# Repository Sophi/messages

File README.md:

# messages
WIP! Visit the project page
sophikravitz.com/messages

Messages from Space is an immersive sound installation built around a simple, true fact: cosmic rays from outer space are passing through your body right now. You cannot feel them. You cannot see them. But they are there. Our custom sensors measure these particles as they pass through the installation, activating sounds, lights, and stories all around you. Participants listen to the experience and view the lights and sculptures. They do not actively interact, but may pause along the path to rest, reflect, or watch the world unfold.

The installation is designed for one visitor or a small group moving at their own pace. Visitors move through several planetary sculptures (12” - 24” diameter) mounted at varying heights. The sculptures are arranged on a path held together by a gentle multi-channel ambient soundscape that gives the space a warm, immersive feeling. When a particle arrives from deep space and passes through a sculpture, roughly every few seconds, it activates a piece of the story, a conversation, a sound effect. Because the detections are real and random, no two experiences are identical: you might wait in silence between sculptures, or hear several conversations in quick succession.

The conversations belong to people living in the near-far future. They speak casually and intimately, sharing small moments of life in a world that is different but not unrecognizable, better in some ways, resilient and human. A doctor coaxing a child through heart surgery. Two centenarians rocking on a porch, remembering war. A young woman savoring chocolate that adapts to her tongue. An old man choosing which hip to replace.

Threading through all of it is Liz. Liz is 126 years old and has chosen the date of her death. Before she goes, she uploads her memories to the archive. She is your guide. Her voice connects the sculptures, reflecting on what she's witnessed across a century and a quarter of living, loving, losing, and staying connected through the Fire-Flood Years and the great dispersal, civilization-scale events that have reshaped the past hundred years.

Team:
Sofy Yuditskaya
Ria Rajan
Sophi Kravitz
Oliver Tanner

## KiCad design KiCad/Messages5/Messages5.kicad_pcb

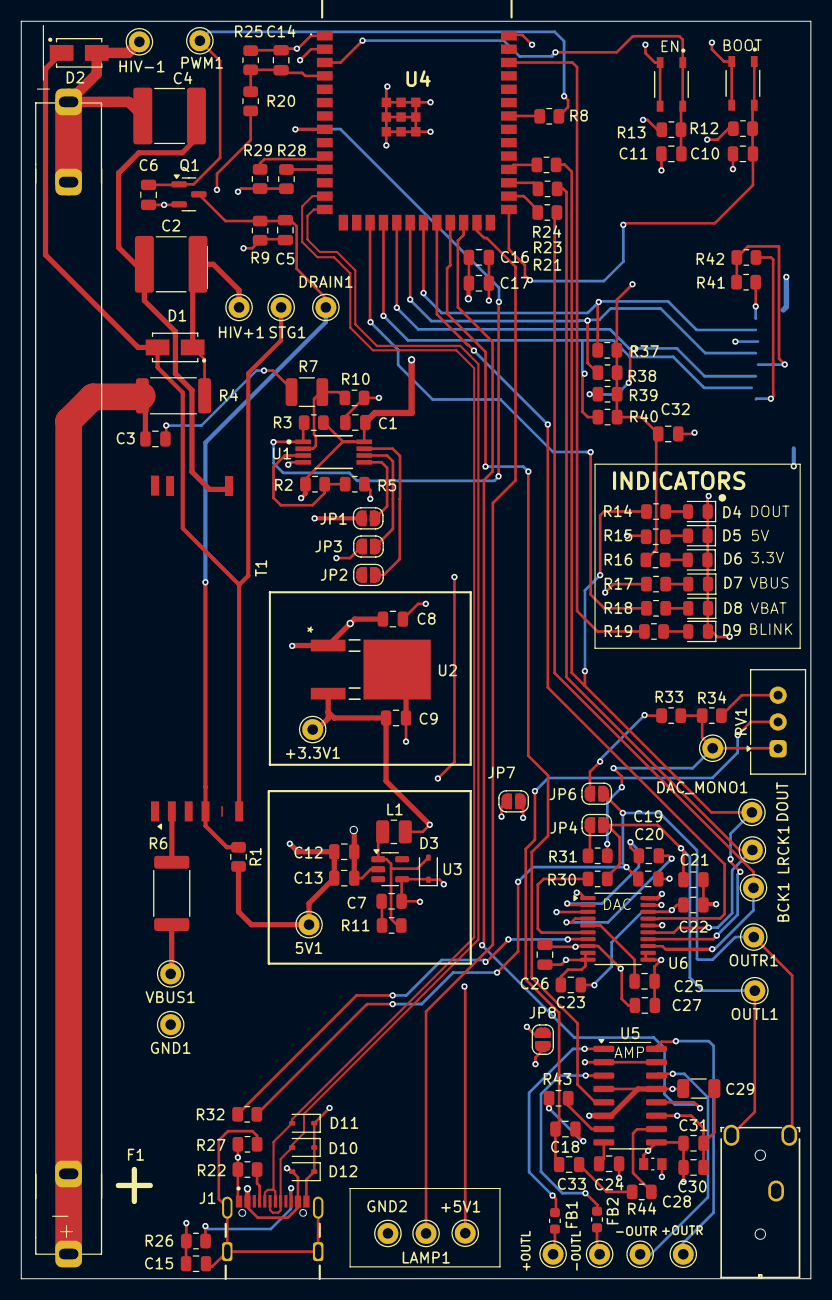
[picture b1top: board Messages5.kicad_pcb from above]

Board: 4 copper layers, 75.0 x 119.5 mm, 134 parts (1 on the bottom side), 81 nets.

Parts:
5V1: TestPoint; Pin_D1.0mm_L10.0mm
+3.3V1, +5V1: TestPoint; Pin_D1.0mm_L10.0mm
+OUTL: TestPoint; Pin_D1.0mm_L10.0mm
+OUTR: TestPoint; Pin_D1.0mm_L10.0mm
-OUTL: TestPoint; Pin_D1.0mm_L10.0mm
-OUTR: TestPoint; Pin_D1.0mm_L10.0mm
BCK1: TestPoint; Pin_D1.0mm_L10.0mm
C1, C10, C11, C14, C23, C27, C30: 0.1uF; C_0805_2012Metric
C2, C4: 1uF/ 500V; C_2220_5750Metric
C3, C5: 1000pF; C_0805_2012Metric
C6: 100pF; C_0805_2012Metric
C7: 120pF; C_0805_2012Metric
C8, C9, C12, C13, C16, C22, C26: 10uF; C_0805_2012Metric
C15: 0.01uF; C_0805_2012Metric
C17, C18, C24, C31, C32, C33: 1uF; C_0805_2012Metric
C19, C25: 2.2uF; C_0805_2012Metric
C20, C21: 2.2nF; C_0805_2012Metric
C28: 20uF; CAPC1810X80N
C29: 220uF; C_1206_3216Metric
D1, D2: ES1H; DIOM4226X244N
D3: D_Schottky; D_SOD-323
D4, D5, D6, D8, D9: YELLOW; LED_0805_2012Metric
D7: BLUE; LED_0805_2012Metric
D10, D11, D12: PESD5V0S1BA; D_SOD-323
DAC_MONO1: TestPoint; Pin_D1.0mm_L10.0mm
DOUT1: TestPoint; Pin_D1.0mm_L10.0mm
DRAIN1: TestPoint; Pin_D1.0mm_L10.0mm
F1: Clip; Fuseholder_Clip-7.62mm_Littelfuse
FB1, FB2: FerriteBead_Small; L_0603_1608Metric
GND1, GND2: TestPoint; Pin_D1.0mm_L10.0mm
HIV+1: TestPoint; Pin_D1.0mm_L10.0mm
HIV-1: TestPoint; Pin_D1.0mm_L10.0mm
J1: USB4105-GF-A; GCT_USB4105-GF-A
J2: AUDIO JACK; STX-3000_KYC
J3: MEM2061-01-188-00-A; MEM2061-01-188-00-A_GCT
JP1, JP2, JP3, JP4, JP6, JP7, JP8: SolderJumper_2_Open; SolderJumper-2_P1.3mm_Open_RoundedPad1.0x1.5mm
L1: 2.2uH; L_1008_2520Metric
LAMP1: TestPoint; Pin_D1.0mm_L10.0mm
LRCK1: TestPoint; Pin_D1.0mm_L10.0mm
OUTL1: TestPoint; Pin_D1.0mm_L10.0mm
OUTR1: TestPoint; Pin_D1.0mm_L10.0mm
PWM1: TestPoint; Pin_D1.0mm_L10.0mm
Q1: AO3400A; SOT-23
R1, R14, R15, R16, R17, R18, R19: 220R; R_0805_2012Metric
R2: 22k; R_0805_2012Metric
R3, R5, R10, R12, R13, R25, R28, R29, R31, R33, R34, R43, R44: 10k; R_0805_2012Metric
R4: 560k, 1M; R_2512_6332Metric
R6: 10R; R_2512_6332Metric
R7: 1M; R_1210_3225Metric
R8: 1K; R_0805_2012Metric
R9: 100R; R_0805_2012Metric
R11: 10R; R_0805_2012Metric
R20: 2.7k; R_0805_2012Metric
R21, R23, R24: 33R; R_0805_2012Metric
R22, R26: 5.1k; R_0805_2012Metric
R27: 1M; R_0805_2012Metric
R30, R32: 470R; R_0805_2012Metric
R37, R38, R39, R40, R41, R42: 4.7k; R_0805_2012Metric
RV1: R_Potentiometer; Potentiometer_Vishay_T93YA_Vertical
S1, S2: SKRPABE010; SW_SKRPABE010
STG1: TestPoint; Pin_D1.0mm_L10.0mm
T1: FL2810-1L; Transformer_Coilcraft_FL2810-1L
U1: LM393BIPWR; PW0008A-MFG
U2: AP7363-33D-13; TO252-3L_DIO
U3: TPS613222ADBV; SOT-23-5
U4: ESP32-S3-WROOM-1-N8; ESP32S3WROOM1N8R2
U5: PAM8406DR; SOP-16_3.9x9.9mm_P1.27mm
U6: PCM5102; TSSOP-20_4.4x6.5mm_P0.65mm
VBUS1: TestPoint; Pin_D1.0mm_L10.0mm

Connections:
+3.3V: +3.3V1.1, C1.2, C9.1, C16.1, C17.1, C26.1, C27.1, C32.1, J3.P4 (VDD), JP1.2 (B), L1.1, R2.2, R3.2, R12.2, R13.2, R16.2, R28.2, R29.2, R37.1, R38.1, R39.1, R40.1, R41.2, R42.2, U1.8 (VCC), U2.3 (OUT), U4.2 (3V3), U6.1 (CPVDD), U6.8 (AVDD), U6.20 (DVDD)
+5V: 5V1.1, +5V1.1, C7.1, C12.1, C13.1, D3.1 (K), R1.2, R15.2, U3.4 (VOUT)
/AMP: U4.24 (IO47), U5.12 (~SHND)
/Audio4/AMP_MONO: C18.2, C33.2, RV1.2
/Audio4/DAC_MONO: DAC_MONO1.1, R31.1, R33.1, R34.1, RV1.1
/Audio4/OUTL: C21.1, J2.2, JP4.2 (B), OUTL1.1, R30.1
/Audio4/OUTR: C20.1, J2.3, JP6.2 (B), OUTR1.1, R32.1
/Audio4/POT_OUTL: R43.1, U5.7 (INL)
/Audio4/POT_OUTR: R44.1, U5.10 (INR)
/BAT_SENSE: R18.2, U4.17 (IO9)
/BLINK: R19.2, U4.38 (IO2)
/CS: J3.P2 (DAT3/CS), R40.2, U4.18 (IO10/CS)
/EN: C11.2, R13.1, S2.1, S2.2, U4.3 (EN)
/GPIO0: C10.2, R12.1, S1.1, S1.2, U4.27 (IO0)
/I2S_BCK: BCK1.1, R21.1, U6.13 (BCK)
/I2S_DOUT: DOUT1.1, R14.2, R24.1, U6.14 (DIN)
/I2S_LRCK: LRCK1.1, R23.1, U6.15 (LRCK)
/LAMP: LAMP1.1, U4.25 (IO48)
/MCU4/SHELL_GND: C15.2, J1.SH1 (SHELL_GND), J1.SH2 (SHELL_GND), J1.SH3 (SHELL_GND), J1.SH4 (SHELL_GND), R27.1
/MISO: J3.P7 (DAT0/MISO), R37.2, U4.21 (IO13/MISO)
/MOSI: J3.P3 (CMD/MOSI), R39.2, U4.19 (IO11/MOSI)
/MUTE: U4.22 (IO14), U6.17 (XSMT)
/MUTE_AMP: U4.23 (IO21), U5.5 (~MUTE)
/PWM: R8.2, U4.34 (IO41)
/Power4/ANODE: C3.1, F1.1, R4.1
/Power4/CATHODE: C4.1, D2.2 (A), F1.2, HIV-1.1
/RAD_IN: R3.1, U1.1 (1OUT), U4.8 (IO15)
/SCK: J3.P5 (SCLK), R38.2, U4.20 (IO12/CLK)
/SCL: R29.1, U4.10 (IO17)
/SDA: R28.1, U4.11 (IO18)
/USB_D+: D10.2, J1.A6 (DP+), J1.B6 (DP2+), U4.14 (IO20)
/USB_D-: D11.2, J1.A7 (DN-), J1.B7 (DN2-), U4.13 (IO19)
AGND: C20.2, C21.2, C22.2, C23.2, C25.2, C26.2, C27.2, J2.1, JP7.1 (A), JP8.2 (B), R34.2, RV1.3, U6.3 (CPGND), U6.9 (AGND), U6.10 (DEMP), U6.11 (FLT), U6.12 (SCK), U6.16 (FMT), U6.19 (DGND)
GND: C1.1, C5.2, C6.2, C8.2, C9.2, C10.1, C11.1, C12.2, C13.2, C14.2, C15.1, C16.2, C17.2, C32.2, D4.1 (K), D5.1 (K), D6.1 (K), D7.1 (K), D8.1 (K), D9.1 (K), D10.1, D11.1, D12.1, GND1.1, GND2.1, J1.A1_B12 (GND), J1.B1_A12 (GND), J3.11 (GROUND), J3.12 (GROUND), J3.P6 (VSS), JP3.2 (B), JP7.2 (B), Q1.2 (S), R5.1, R9.1, R10.1, R22.2, R25.1, R26.2, R27.2, S1.3, S1.4, S2.3, S2.4, U1.4 (GND), U2.2 (GND), U3.2 (GND), U4.1 (GND_1), U4.40 (GND_2), U4.41 (GND_3), U4.42 (GND_4), U4.43 (GND_5), U4.44 (GND_6), U4.45 (GND_7), U4.46 (GND_8), U4.47 (GND_9), U4.48 (GND_10), U4.49 (GND_11)
unnamed: +OUTL.1, FB1.1
unnamed: -OUTL.1, FB2.1
unnamed: C2.1, C4.2, T1.7
unnamed: C3.2, R7.2
unnamed: C7.2, R11.1
unnamed: C18.1, R43.2
unnamed: C33.1, R44.2
unnamed: D1.2 (A), D2.1 (K), STG1.1, T1.6
unnamed: C2.2, D1.1 (K), HIV+1.1, R4.2
unnamed: D3.2 (A), L1.2, R11.2, U3.1 (SW)
unnamed: D4.2 (A), R14.1
unnamed: D5.2 (A), R15.1
unnamed: D6.2 (A), R16.1
unnamed: D7.2 (A), R17.1
unnamed: D8.2 (A), R18.1
unnamed: D9.2 (A), R19.1
unnamed: J1.A5 (CC1), R22.1
unnamed: J1.B5 (CC2), R26.1
unnamed: J3.P8 (DAT1), R41.1
unnamed: J3.P1 (DAT2), R42.1
unnamed: JP1.1 (A), U1.5 (2IN+)
unnamed: JP2.2 (B), U1.7 (2OUT)
unnamed: JP3.1 (A), U1.6 (2IN-)
unnamed: JP4.1 (A), R31.2
unnamed: JP6.1 (A), R33.2
unnamed: C5.1, DRAIN1.1, Q1.3 (D), R1.1, R9.2, T1.4
unnamed: C6.1, PWM1.1, Q1.1 (G), R8.1
unnamed: R6.1, T1.2
unnamed: R2.1, R5.2, U1.3 (1IN+)
unnamed: R7.1, R10.2, U1.2 (1IN-)
unnamed: C14.1, R20.1, R25.2, U4.4 (IO4/ADC1_CH3)
unnamed: R21.2, U4.28 (IO35)
unnamed: R23.2, U4.29 (IO36)
unnamed: R24.2, U4.30 (IO37)
unnamed: FB1.2, U5.1 (+OUT_L)
unnamed: +OUTR.1, U5.16 (+OUT_R)
unnamed: FB2.2, U5.3 (-OUT_L)
unnamed: -OUTR.1, U5.14 (-OUT_R)
unnamed: C24.1, U5.8 (VREF)
unnamed: C19.2, U6.4 (CAPM)
unnamed: C19.1, U6.2 (CAPP)
unnamed: C22.1, C23.1, U6.18 (LDOO)
unnamed: R30.2, U6.6 (OUTL)
unnamed: R32.2, U6.7 (OUTR)
unnamed: C25.1, U6.5 (VNEG)
PGND: C24.2, C28.2, C29.2, C30.2, C31.2, JP8.1 (A), U5.2 (PGNDL), U5.11 (GND), U5.15 (PGNDR)
VBUS: C8.1, C28.1, C29.1, C30.1, C31.1, D12.2, J1.A4_B9 (VBUS), J1.B4_A9 (VBUS), R6.2, R17.2, R20.2, U2.1 (IN), U5.4 (PVDDL), U5.6 (VDD), U5.9 (MODE), U5.13 (PVDDR), VBUS1.1

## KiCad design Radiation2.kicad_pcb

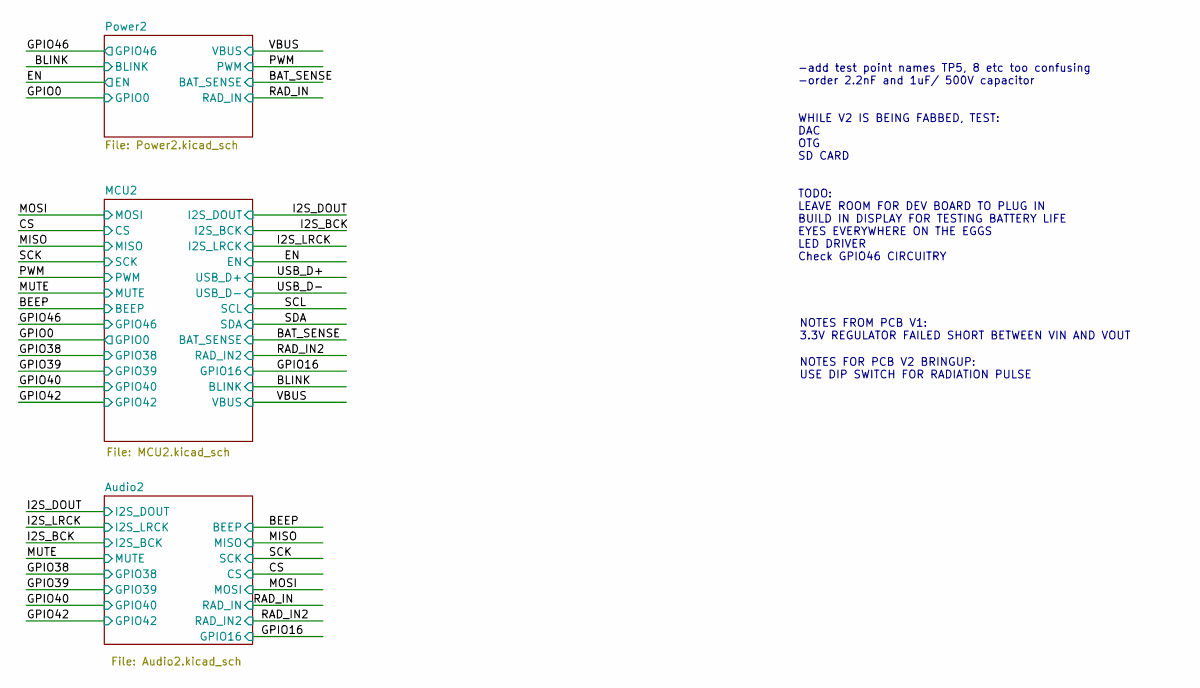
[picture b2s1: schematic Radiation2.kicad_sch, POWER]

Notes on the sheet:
-add test point names TP5, 8 etc too confusing -order 2.2nF and 1uF/ 500V capacitor WHILE V2 IS BEING FABBED, TEST: DAC OTG SD CARD TODO: LEAVE ROOM FOR DEV BOARD TO PLUG IN BUILD IN DISPLAY FOR TESTING BATTERY LIFE EYES EVERYWHERE ON THE EGGS LED DRIVER Check GPIO46 CIRCUITRY
NOTES FOR PCB V2 BRINGUP: USE DIP SWITCH FOR RADIATION PULSE
NOTES FROM PCB V1: 3.3V REGULATOR FAILED SHORT BETWEEN VIN AND VOUT

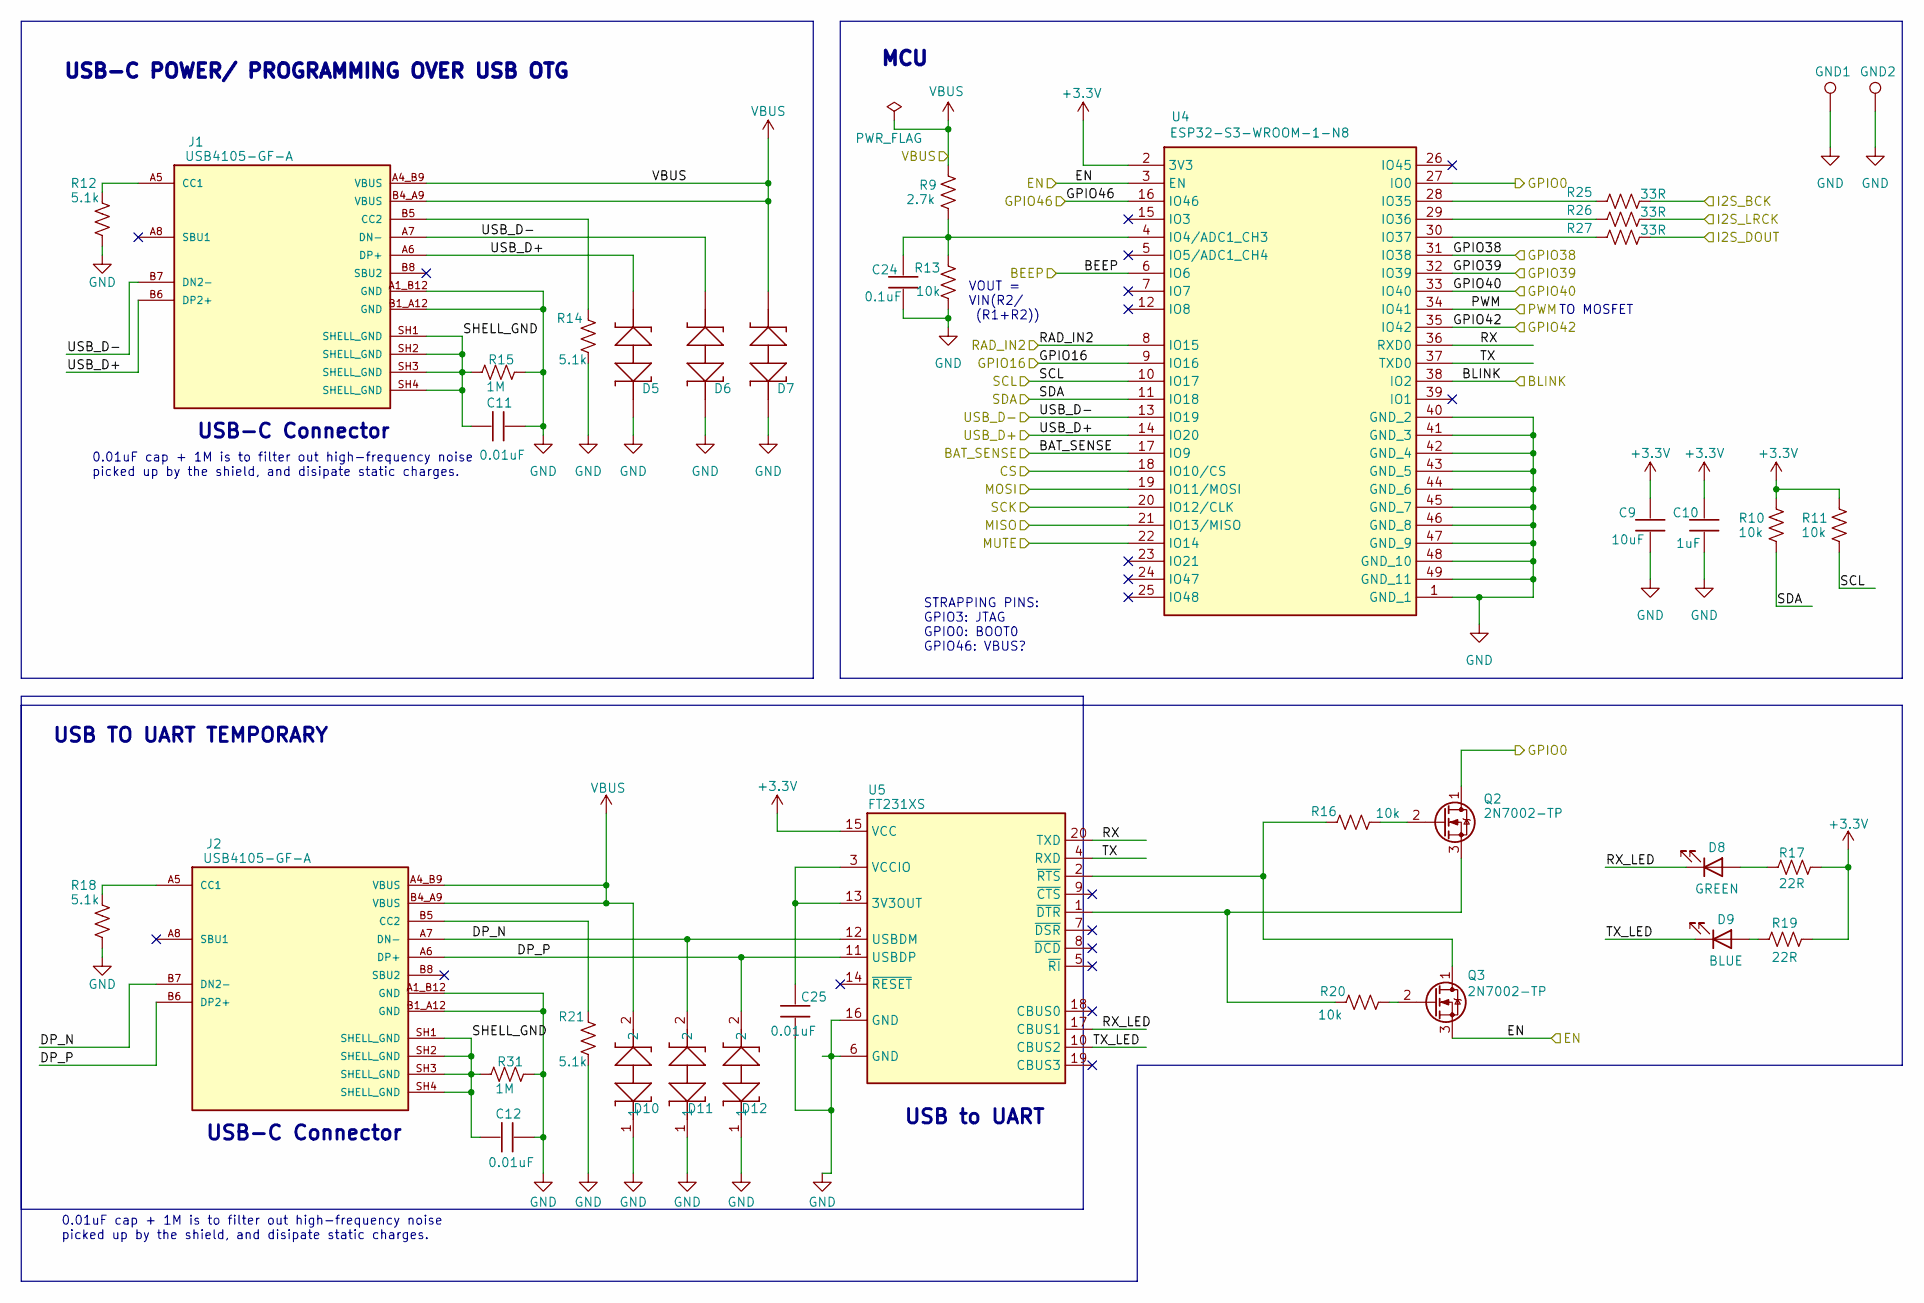
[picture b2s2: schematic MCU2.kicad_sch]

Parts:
C9: 10uF; C_0805_2012Metric; MPN CL21B106KPQNNNE
C10: 1uF; C_0805_2012Metric; MPN CC0805KKX5R6BB105
C11, C12, C25: 0.01uF; C_0805_2012Metric; MPN C0805C103K5RACTU
C24: 0.1uF; C_0805_2012Metric; MPN CC0805KRX7R9BB104
D5, D6, D7, D10, D11, D12: PESD5V0S1BA; SOD323_NXP; MPN PESD5V0S1BA,115
D8: GREEN; LED_0805_2012Metric; MPN 150080GS75000
D9: BLUE; LED_0805_2012Metric; MPN 150080BS75000
GND1, GND2: TestPoint; Pin_D1.0mm_L10.0mm
J1, J2: USB4105-GF-A; GCT_USB4105-GF-A; MPN USB4105-GF-A
Q2, Q3: 2N7002-TP; SOT-23; MPN 2N7002-TP
R9: 2.7k; R_0805_2012Metric; MPN CRG0805F2K7
R10, R11, R13, R16, R20: 10k; R_0805_2012Metric; MPN RMCF0805FT10K0
R12, R14, R18, R21: 5.1k; R_0805_2012Metric; MPN RC0805JR-075K1L
R15, R31: 1M; R_0805_2012Metric; MPN RC0805JR-071ML
R17, R19: 22R; R_0805_2012Metric; MPN RC0805FR-0722RL
R25, R26, R27: 33R; R_0805_2012Metric; MPN RC0805FR-0733RL
U4: ESP32-S3-WROOM-1-N8; ESP32S3WROOM1N8R2; Mouser Part Number 356-ESP32-S3WROOM1N8
U5: FT231XS; SSOP-20_3.9x8.7mm_P0.635mm; MPN FT231XS-R

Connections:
+3.3V: C9.1, C10.1, R10.2, R11.2, R17.1, R19.1, U4.2 (3V3), U5.15 (VCC); also elsewhere on the board
/BAT_SENSE: U4.17 (IO9); also elsewhere on the board
/BEEP: U4.6 (IO6); also elsewhere on the board
/BLINK: U4.38 (IO2); also elsewhere on the board
/CS: U4.18 (IO10/CS); also elsewhere on the board
/EN: Q3.3 (S), U4.3 (EN); also elsewhere on the board
/GPIO0: Q2.1 (D), U4.27 (IO0); also elsewhere on the board
/GPIO16: U4.9 (IO16); also elsewhere on the board
/GPIO38: U4.31 (IO38); also elsewhere on the board
/GPIO39: U4.32 (IO39); also elsewhere on the board
/GPIO40: U4.33 (IO40); also elsewhere on the board
/GPIO42: U4.35 (IO42); also elsewhere on the board
/GPIO46: U4.16 (IO46); also elsewhere on the board
/I2S_BCK: R25.1; also elsewhere on the board
/I2S_DOUT: R27.1; also elsewhere on the board
/I2S_LRCK: R26.1; also elsewhere on the board
/MCU2/DP_N: D11.2, J2.A7 (DN-), J2.B7 (DN2-), U5.12 (USBDM)
/MCU2/DP_P: D12.2, J2.A6 (DP+), J2.B6 (DP2+), U5.11 (USBDP)
/MCU2/RX: U4.36 (RXD0), U5.20 (TXD)
/MCU2/RX_LED: D8.1 (K), U5.17 (CBUS1)
/MCU2/SHELL_GND: C11.2, C12.2, J1.SH1 (SHELL_GND), J1.SH2 (SHELL_GND), J1.SH3 (SHELL_GND), J1.SH4 (SHELL_GND), J2.SH1 (SHELL_GND), J2.SH2 (SHELL_GND), J2.SH3 (SHELL_GND), J2.SH4 (SHELL_GND), R15.1, R31.1
/MCU2/TX: U4.37 (TXD0), U5.4 (RXD)
/MCU2/TX_LED: D9.1 (K), U5.10 (CBUS2)
/MISO: U4.21 (IO13/MISO); also elsewhere on the board
/MOSI: U4.19 (IO11/MOSI); also elsewhere on the board
/MUTE: U4.22 (IO14); also elsewhere on the board
/PWM: U4.34 (IO41); also elsewhere on the board
/RAD_IN2: U4.8 (IO15); also elsewhere on the board
/SCK: U4.20 (IO12/CLK); also elsewhere on the board
/SCL: R11.1, U4.10 (IO17)
/SDA: R10.1, U4.11 (IO18)
/USB_D+: D5.2, J1.A6 (DP+), J1.B6 (DP2+), U4.14 (IO20)
/USB_D-: D6.2, J1.A7 (DN-), J1.B7 (DN2-), U4.13 (IO19)
GND: C9.2, C10.2, C11.1, C12.1, C24.2, C25.1, D5.1, D6.1, D7.1, D10.1, D11.1, D12.1, GND1.1, GND2.1, J1.A1_B12 (GND), J1.B1_A12 (GND), J2.A1_B12 (GND), J2.B1_A12 (GND), R12.2, R13.1, R14.2, R15.2, R18.2, R21.2, R31.2, U4.1 (GND_1), U4.40 (GND_2), U4.41 (GND_3), U4.42 (GND_4), U4.43 (GND_5), U4.44 (GND_6), U4.45 (GND_7), U4.46 (GND_8), U4.47 (GND_9), U4.48 (GND_10), U4.49 (GND_11), U5.6 (GND), U5.16 (GND); also elsewhere on the board
unnamed: D8.2 (A), R17.2
unnamed: D9.2 (A), R19.2
unnamed: J1.A5 (CC1), R12.1
unnamed: J1.B5 (CC2), R14.1
unnamed: J2.A5 (CC1), R18.1
unnamed: J2.B5 (CC2), R21.1
unnamed: Q2.2 (G), R16.1
unnamed: Q2.3 (S), R20.2, U5.1 (~DTR)
unnamed: Q3.1 (D), R16.2, U5.2 (~RTS)
unnamed: Q3.2 (G), R20.1
unnamed: C24.1, R9.1, R13.2, U4.4 (IO4/ADC1_CH3)
unnamed: R25.2, U4.28 (IO35)
unnamed: R26.2, U4.29 (IO36)
unnamed: R27.2, U4.30 (IO37)
unnamed: C25.2, U5.3 (VCCIO), U5.13 (3V3OUT)
VBUS: D7.2, D10.2, J1.A4_B9 (VBUS), J1.B4_A9 (VBUS), J2.A4_B9 (VBUS), J2.B4_A9 (VBUS), R9.2; also elsewhere on the board

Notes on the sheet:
USB-C POWER/ PROGRAMMING OVER USB OTG
0.01uF cap + 1M is to filter out high-frequency noise picked up by the shield, and disipate static charges.
MCU
VOUT = VIN(R2/ (R1+R2))
USB TO UART TEMPORARY
TO MOSFET
USB-C Connector
STRAPPING PINS: GPIO3: JTAG GPIO0: BOOT0 GPIO46: VBUS?
USB to UART

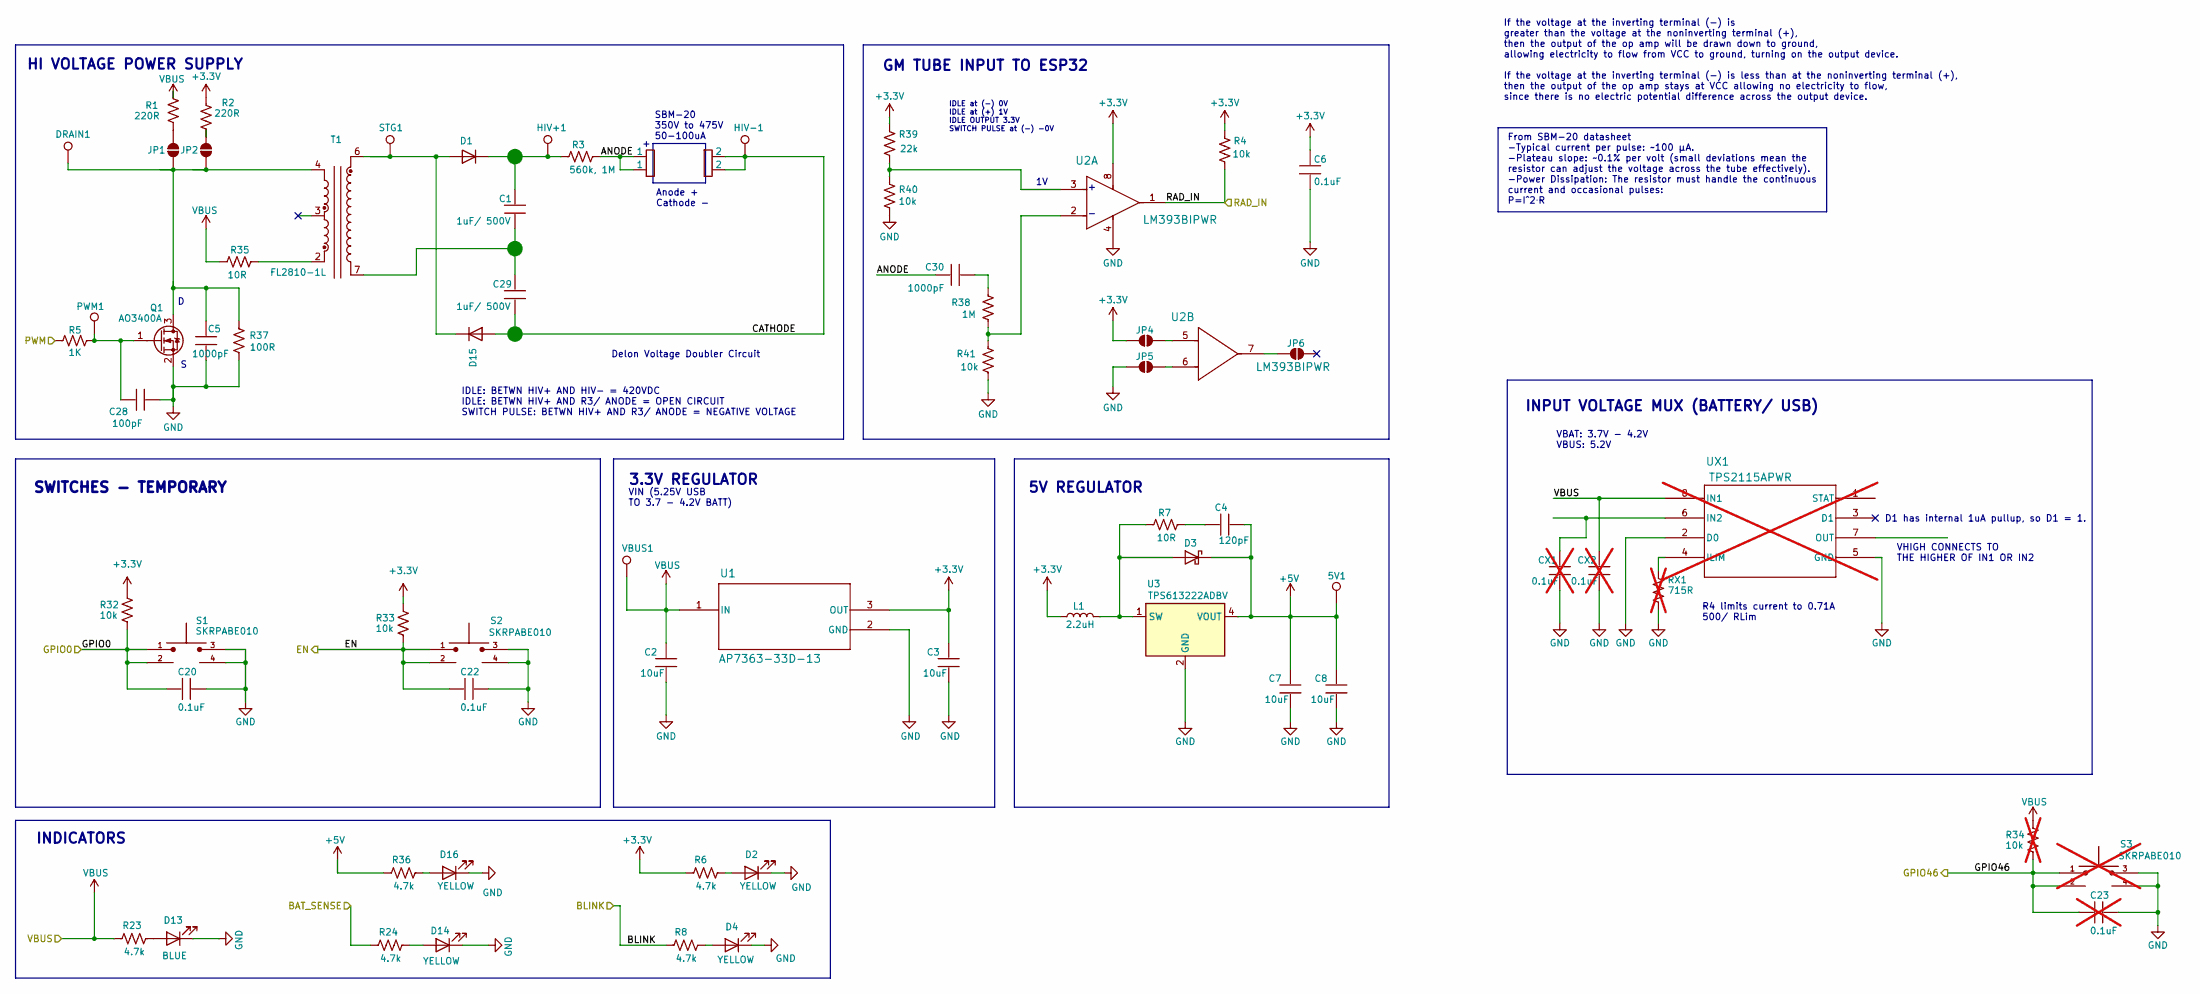
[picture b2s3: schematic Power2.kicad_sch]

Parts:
5V1: TestPoint; Pin_D1.0mm_L10.0mm
C1, C29: 1uF/ 500V; C_2220_5750Metric; MPN ECW-FD2J105K
C2, C3, C7, C8: 10uF; C_0805_2012Metric; MPN CL21B106KPQNNNE
C4: 120pF; C_0805_2012Metric; MPN C0805C121J5GACTU
C5, C30: 1000pF; C_0805_2012Metric; MPN C2012C0G2W102J060AA
C6, C20, C22: 0.1uF; C_0805_2012Metric; MPN CC0805KRX7R9BB104
C23: 0.1uF; C_0805_2012Metric; MPN CC0805KRX7R9BB104; not fitted
C28: 100pF; C_0805_2012Metric; MPN C0805C101J5GACTU
CX1, CX2: 0.1uF; C_0805_2012Metric; MPN CC0805KRX7R9BB104; not fitted
D1, D15: ES1H; DIOM4226X244N; MPN ES1H
D2, D4, D14, D16: YELLOW; LED_0805_2012Metric; MPN 150080YS75000
D3: D_Schottky; D_SOD-323; MPN 1SS367,H3F
D13: BLUE; LED_0805_2012Metric; MPN 150080BS75000
DRAIN1: TestPoint; Pin_D1.0mm_L10.0mm
F1: Clip; Fuseholder_Clip-7.62mm_Littelfuse; MPN 01220088Z
HIV+1: TestPoint; Pin_D1.0mm_L10.0mm
HIV-1: TestPoint; Pin_D1.0mm_L10.0mm
JP1, JP2, JP4, JP5, JP6: SolderJumper_2_Open; SolderJumper-2_P1.3mm_Open_RoundedPad1.0x1.5mm
L1: 2.2uH; L_1008_2520Metric; MPN DFE252012F-2R2M=P2
PWM1: TestPoint; Pin_D1.0mm_L10.0mm
Q1: AO3400A; SOT-23; MPN AO3400A
R1, R2: 220R; R_0805_2012Metric; MPN RK73B2ATTD221J
R3: 560k, 1M; R_2512_6332Metric; MPN CRGP2512F560K
R4: 10k; R_0805_2012Metric; MPN CRCW08054K70FKEAC
R5: 1K; R_0805_2012Metric; MPN RNCP0805FTD1K00
R6, R8, R23, R24, R36: 4.7k; R_0805_2012Metric; MPN CRCW08054K70FKEAC
R7: 10R; R_0805_2012Metric; MPN RMCF0603FT10R0
R32, R33, R40, R41: 10k; R_0805_2012Metric; MPN RMCF0805FT10K0
R34: 10k; R_0805_2012Metric; MPN RMCF0805FT10K0; not fitted
R35: 10R; R_2512_6332Metric; MPN 352210RJT
R37: 100R; R_0805_2012Metric; MPN ERJ-P06J101V
R38: 1M; R_1210_3225Metric; MPN RC1210FR-071ML
R39: 22k; R_0805_2012Metric; MPN RMCF0805JT22K0
RX1: 715R; R_0805_2012Metric; MPN CRCW0805715RFKEA; not fitted
S1, S2: SKRPABE010; SW_SKRPABE010; MPN SKRPABE010
S3: SKRPABE010; SW_SKRPABE010; MPN SKRPABE010; not fitted
STG1: TestPoint; Pin_D1.0mm_L10.0mm
T1: FL2810-1L; Transformer_Coilcraft_FL2810-1L; MPN FL2810-1L; Mouser Part Number 580-54100C
U1: AP7363-33D-13; TO252-3L_DIO
U2: LM393BIPWR; PW0008A-MFG
U3: TPS613222ADBV; SOT-23-5; MPN TPS613222ADBV
UX1: TPS2115APWR; PW8; MPN TPS2115APWR; not fitted
VBUS1: TestPoint; Pin_D1.0mm_L10.0mm

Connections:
+3.3V: C3.1, C6.2, JP4.2 (B), L1.1, R2.2, R4.2, R6.2, R32.2, R33.2, R39.2, U1.3 (OUT), U2.8 (VCC); also elsewhere on the board
+5V: 5V1.1, C4.1, C7.1, C8.1, D3.1 (K), R36.2, U3.4 (VOUT)
/BAT_SENSE: R24.2; also elsewhere on the board
/BLINK: R8.2; also elsewhere on the board
/EN: C22.2, R33.1, S2.1, S2.2; also elsewhere on the board
/GPIO0: C20.2, R32.1, S1.1, S1.2; also elsewhere on the board
/GPIO46: C23.2, R34.1, S3.1, S3.2; also elsewhere on the board
/PWM: R5.2; also elsewhere on the board
/Power2/ANODE: C30.1, F1.1, R3.1
/Power2/CATHODE: C29.1, D15.2 (A), F1.2, HIV-1.1
/RAD_IN: R4.1, U2.1 (1OUT); also elsewhere on the board
GND: C2.2, C3.2, C5.2, C6.1, C7.2, C8.2, C20.1, C22.1, C23.1, C28.2, CX1.2, CX2.2, D2.1 (K), D4.1 (K), D13.1 (K), D14.1 (K), D16.1 (K), JP5.2 (B), Q1.2 (S), R37.1, R40.1, R41.1, RX1.1, S1.3, S1.4, S2.3, S2.4, S3.3, S3.4, U1.2 (GND), U2.4 (GND), U3.2 (GND), UX1.2 (D0), UX1.5 (GND); also elsewhere on the board
unnamed: C1.1, C29.2, T1.7
unnamed: C4.2, R7.1
unnamed: C30.2, R38.2
unnamed: CX1.1, UX1.6 (IN2)
unnamed: CX2.1, UX1.8 (IN1)
unnamed: D1.2 (A), D15.1 (K), STG1.1, T1.6
unnamed: C1.2, D1.1 (K), HIV+1.1, R3.2
unnamed: D2.2 (A), R6.1
unnamed: D3.2 (A), L1.2, R7.2, U3.1 (SW)
unnamed: D4.2 (A), R8.1
unnamed: D13.2 (A), R23.1
unnamed: D14.2 (A), R24.1
unnamed: D16.2 (A), R36.1
unnamed: C5.1, DRAIN1.1, JP1.1 (A), JP2.1 (A), Q1.3 (D), R37.2, T1.4
unnamed: JP1.2 (B), R1.1
unnamed: JP2.2 (B), R2.1
unnamed: JP4.1 (A), U2.5 (2IN+)
unnamed: JP5.1 (A), U2.6 (2IN-)
unnamed: JP6.2 (B), U2.7 (2OUT)
unnamed: C28.1, PWM1.1, Q1.1 (G), R5.1
unnamed: R35.1, T1.2
unnamed: RX1.2, UX1.4 (ILIM)
unnamed: R39.1, R40.2, U2.3 (1IN+)
unnamed: R38.1, R41.2, U2.2 (1IN-)
VBUS: C2.1, R1.2, R23.2, R34.2, R35.2, U1.1 (IN), VBUS1.1; also elsewhere on the board

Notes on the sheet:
5V REGULATOR
D1 has internal 1uA pullup, so D1 = 1.
GM TUBE INPUT TO ESP32
INPUT VOLTAGE MUX (BATTERY/ USB)
INDICATORS
HI VOLTAGE POWER SUPPLY
If the voltage at the inverting terminal (-) is greater than the voltage at the noninverting terminal (+), then the output of the op amp will be drawn down to ground, allowing electricity to flow from VCC to ground, turning on the output device. If the voltage at the inverting terminal (-) is less 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
Delon Voltage Doubler Circuit
From SBM-20 datasheet -Typical current per pulse: ~100 µA. -Plateau slope: ~0.1% per volt (small deviations mean the resistor can adjust the voltage across the tube effectively). -Power Dissipation: The resistor must handle the continuous current and occasional pulses: P=I^2⋅R
R4 limits current to 0.71A 500/ RLim
VIN (5.25V USB TO 3.7 - 4.2V BATT)
3.3V REGULATOR
VHIGH CONNECTS TO THE HIGHER OF IN1 OR IN2
SWITCHES - TEMPORARY
Anode + Cathode -
VBAT: 3.7V - 4.2V VBUS: 5.2V
SBM-20 350V to 475V 50-100uA
IDLE at (-) 0V IDLE at (+) 1V IDLE OUTPUT 3.3V SWITCH PULSE at (-) -0V
IDLE: BETWN HIV+ AND HIV- = 420VDC IDLE: BETWN HIV+ AND R3/ ANODE = OPEN CIRCUIT SWITCH PULSE: BETWN HIV+ AND R3/ ANODE = NEGATIVE VOLTAGE

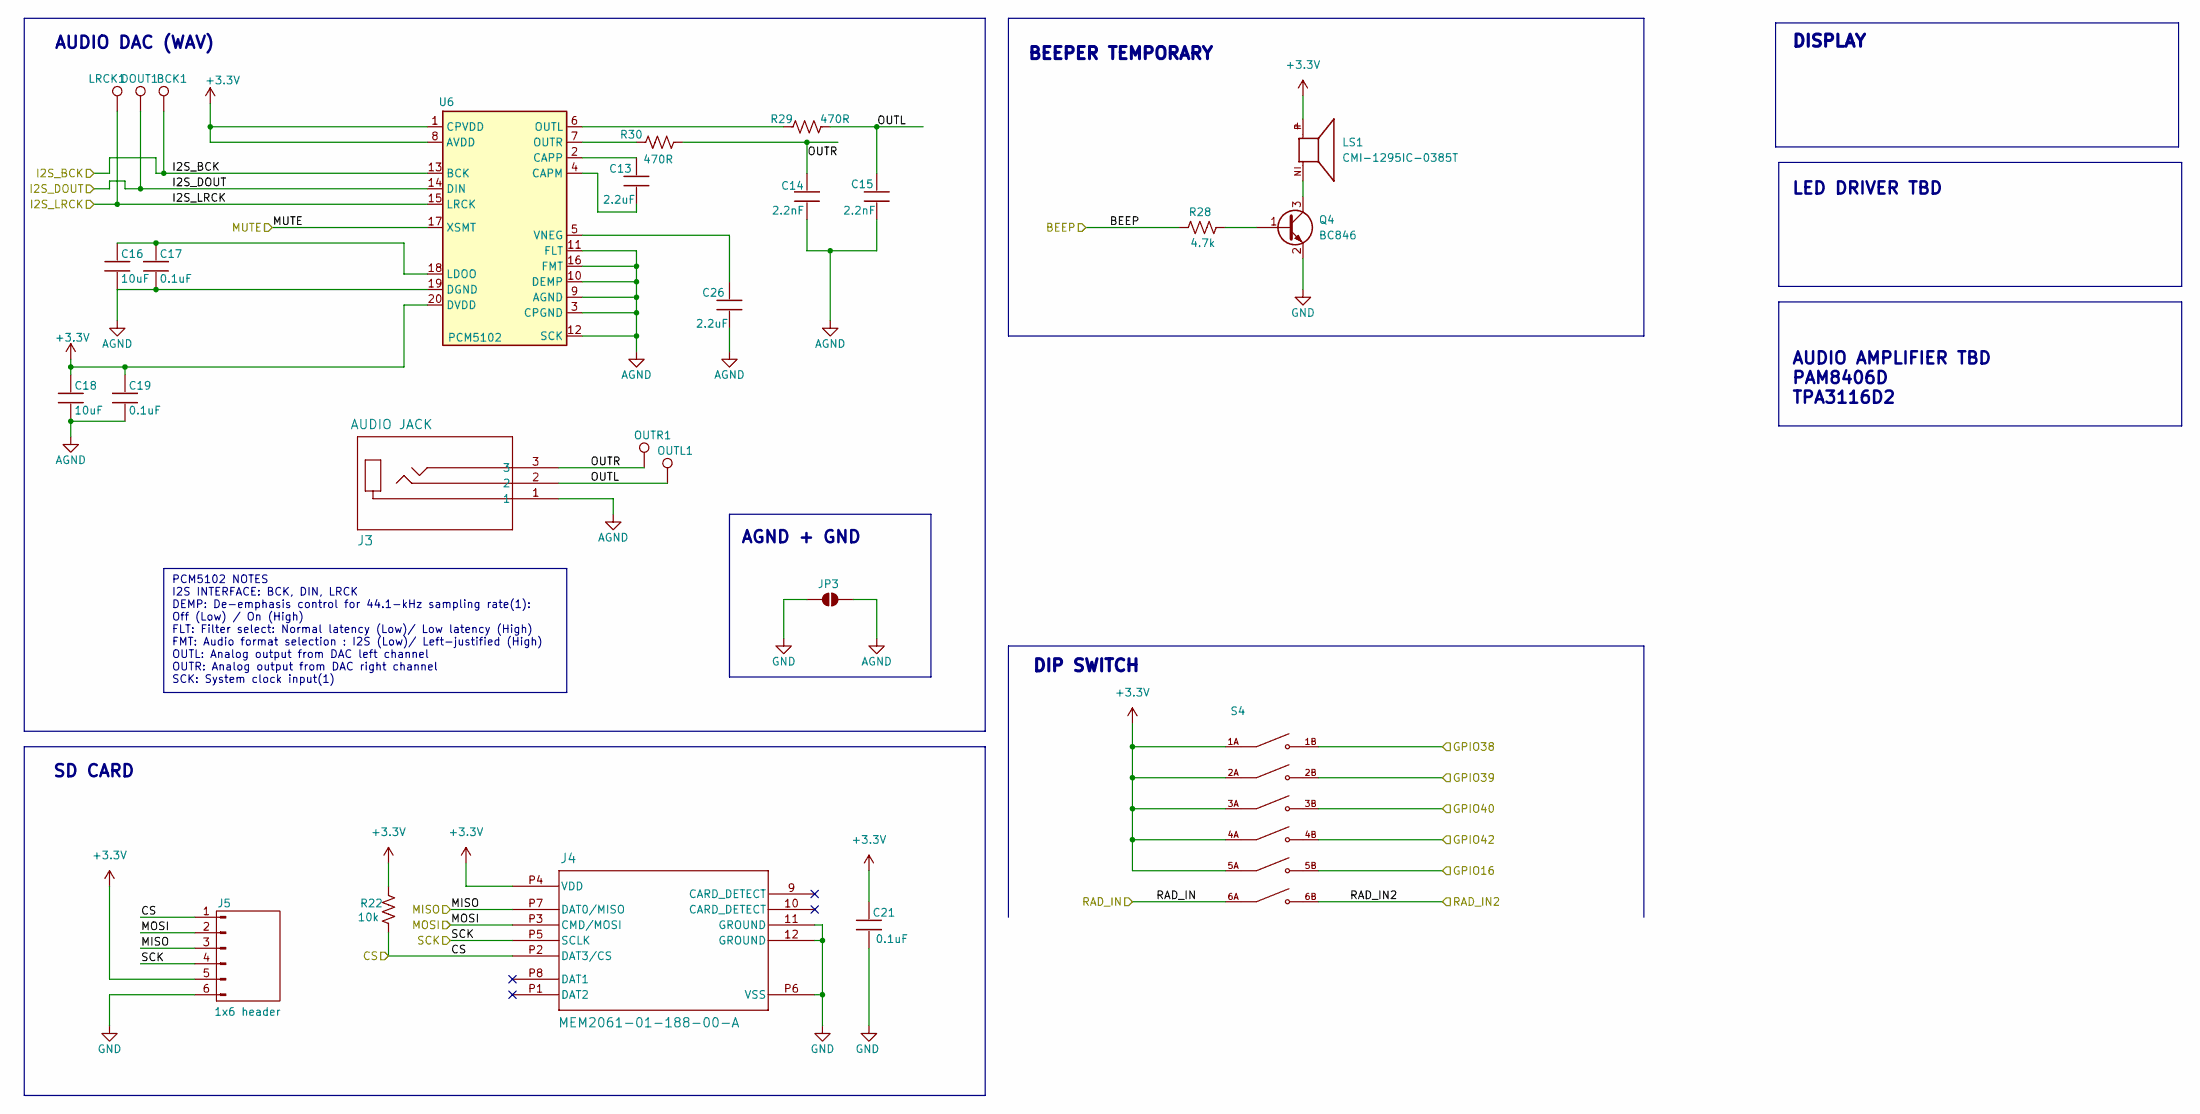
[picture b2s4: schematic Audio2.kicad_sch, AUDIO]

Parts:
BCK1: TestPoint; Pin_D1.0mm_L10.0mm
C13, C26: 2.2uF; C_0805_2012Metric; MPN LMK212BJ225KD-T
C14, C15: 2.2nF; C_0805_2012Metric; MPN C0805C222KCRACTU
C16, C18: 10uF; C_0805_2012Metric; MPN CL21B106KPQNNNE
C17, C19, C21: 0.1uF; C_0805_2012Metric; MPN CC0805KRX7R9BB104
DOUT1: TestPoint; Pin_D1.0mm_L10.0mm
J3: AUDIO JACK; STX-3000_KYC; MPN STX-3000
J4: MEM2061-01-188-00-A; MEM2061-01-188-00-A_GCT; MPN MEM2061-01-188-00-A
J5: 1x6 header; PinHeader_1x06_P2.54mm_Vertical; MPN 61300611121
JP3: SolderJumper_2_Open; SolderJumper-2_P1.3mm_Open_RoundedPad1.0x1.5mm
LRCK1: TestPoint; Pin_D1.0mm_L10.0mm
LS1: CMI-1295IC-0385T; CUI_CMI-1295IC-0385T; MPN CMI-1295IC-0385T
OUTL1: TestPoint; Pin_D1.0mm_L10.0mm
OUTR1: TestPoint; Pin_D1.0mm_L10.0mm
Q4: BC846; SOT-23; MPN BC846
R22: 10k; R_0805_2012Metric; MPN RMCF0805FT10K0
R28: 4.7k; R_0805_2012Metric; MPN CRCW08054K70FKEAC
R29, R30: 470R; R_0805_2012Metric; MPN CRGCQ0805J470R
S4: DS04-254-2-06BK-SMT; DIP SWITCH SW_DS04-254-2-06BK-SMT; MPN DS04-254-2-06BK-SMT
U6: PCM5102; TSSOP-20_4.4x6.5mm_P0.65mm; MPN PCM5102APWR

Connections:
+3.3V: C18.1, C19.1, C21.1, J4.P4 (VDD), J5.5, LS1.P, R22.1, S4.1A, S4.2A, S4.3A, S4.4A, S4.5A, U6.1 (CPVDD), U6.8 (AVDD), U6.20 (DVDD); also elsewhere on the board
/Audio2/OUTL: C15.1, J3.2, OUTL1.1, R29.1
/Audio2/OUTR: C14.1, J3.3, OUTR1.1, R30.1
/BEEP: R28.2; also elsewhere on the board
/CS: J4.P2 (DAT3/CS), J5.1, R22.2; also elsewhere on the board
/GPIO16: S4.5B; also elsewhere on the board
/GPIO38: S4.1B; also elsewhere on the board
/GPIO39: S4.2B; also elsewhere on the board
/GPIO40: S4.3B; also elsewhere on the board
/GPIO42: S4.4B; also elsewhere on the board
/I2S_BCK: BCK1.1, U6.13 (BCK); also elsewhere on the board
/I2S_DOUT: DOUT1.1, U6.14 (DIN); also elsewhere on the board
/I2S_LRCK: LRCK1.1, U6.15 (LRCK); also elsewhere on the board
/MISO: J4.P7 (DAT0/MISO), J5.3; also elsewhere on the board
/MOSI: J4.P3 (CMD/MOSI), J5.2; also elsewhere on the board
/MUTE: U6.17 (XSMT); also elsewhere on the board
/RAD_IN: S4.6A; also elsewhere on the board
/RAD_IN2: S4.6B; also elsewhere on the board
/SCK: J4.P5 (SCLK), J5.4; also elsewhere on the board
AGND: C14.2, C15.2, C16.2, C17.2, C18.2, C19.2, C26.2, J3.1, JP3.2 (B), U6.3 (CPGND), U6.9 (AGND), U6.10 (DEMP), U6.11 (FLT), U6.12 (SCK), U6.16 (FMT), U6.19 (DGND)
GND: C21.2, J4.11 (GROUND), J4.12 (GROUND), J4.P6 (VSS), J5.6, JP3.1 (A), Q4.2 (E); also elsewhere on the board
unnamed: Q4.1 (B), R28.1
unnamed: LS1.N, Q4.3 (C)
unnamed: C13.2, U6.4 (CAPM)
unnamed: C13.1, U6.2 (CAPP)
unnamed: C16.1, C17.1, U6.18 (LDOO)
unnamed: R29.2, U6.6 (OUTL)
unnamed: R30.2, U6.7 (OUTR)
unnamed: C26.1, U6.5 (VNEG)

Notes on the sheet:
LED DRIVER TBD
DIP SWITCH
DISPLAY
AUDIO DAC (WAV)
BEEPER TEMPORARY
PCM5102 NOTES I2S INTERFACE: BCK, DIN, LRCK DEMP: De-emphasis control for 44.1-kHz sampling rate(1): Off (Low) / On (High) FLT: Filter select: Normal latency (Low)/ Low latency (High) FMT: Audio format selection : I2S (Low)/ Left-justified (High) OUTL: Analog output from DAC left channel OUTR: Anal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
AGND + GND
AUDIO AMPLIFIER TBD PAM8406D TPA3116D2
SD CARD

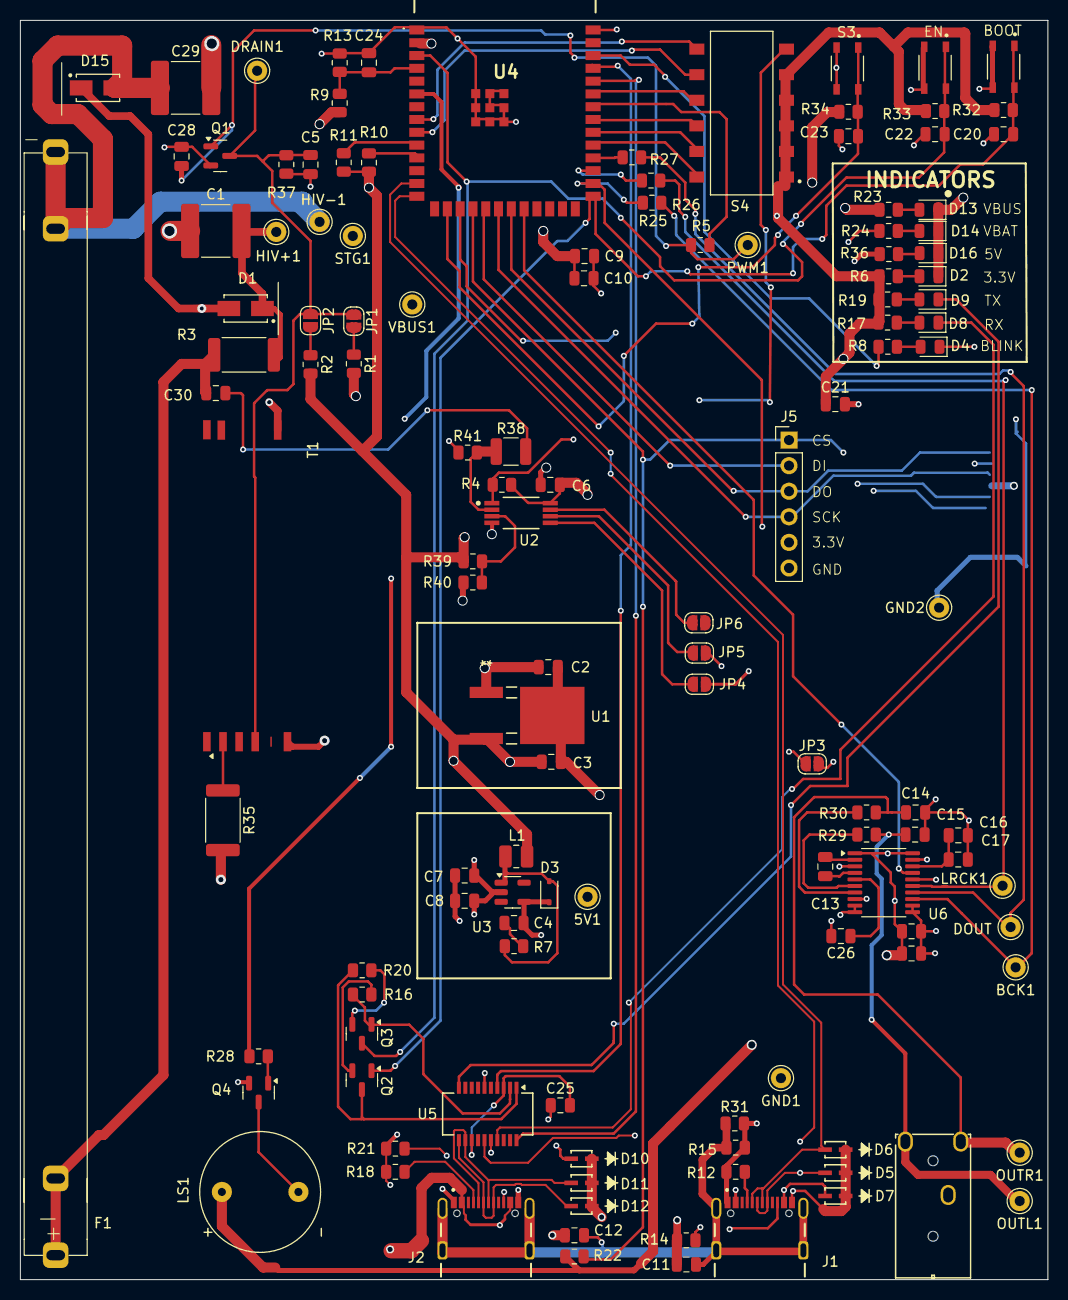
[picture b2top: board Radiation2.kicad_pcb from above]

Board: 4 copper layers, 102.0 x 125.0 mm, 129 parts (1 on the bottom side), 86 nets.

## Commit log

2025-01-31 first schemtic/ PCB upload
2025-01-31 Updated schematics/ pcb
2025-01-31 revisions after design review by Ted Yapo
2025-02-01 proto 1 final
2025-02-20 PCB v2
2025-03-10 update V2
2025-04-11 Adding V3
2025-07-19 remote update
2026-02-15 add Radiation3 archive files
